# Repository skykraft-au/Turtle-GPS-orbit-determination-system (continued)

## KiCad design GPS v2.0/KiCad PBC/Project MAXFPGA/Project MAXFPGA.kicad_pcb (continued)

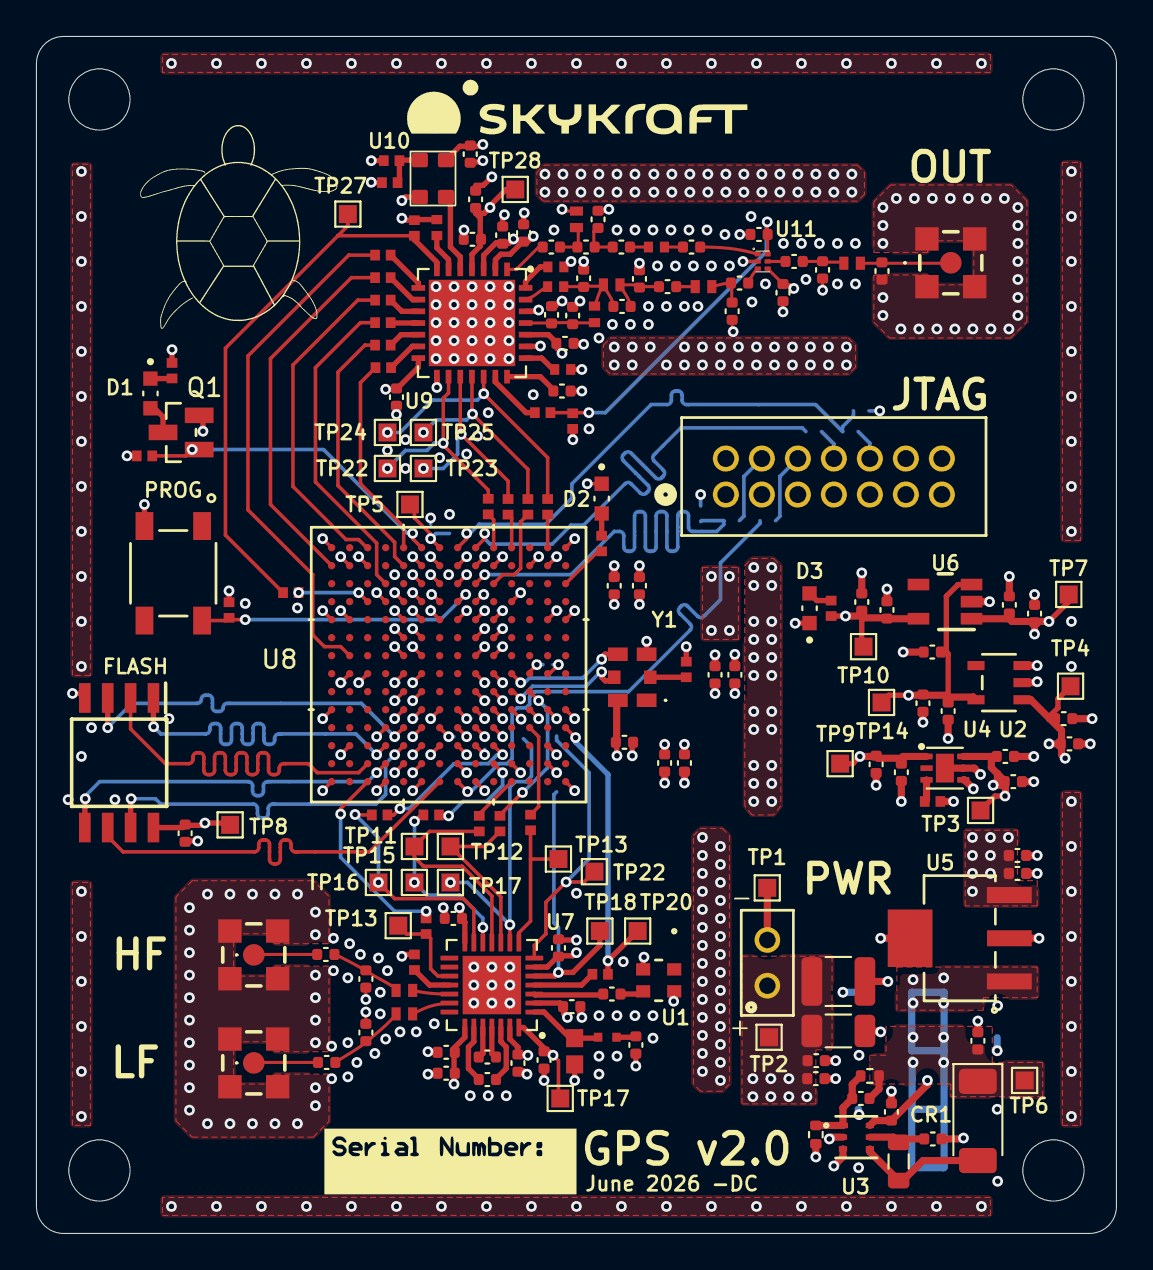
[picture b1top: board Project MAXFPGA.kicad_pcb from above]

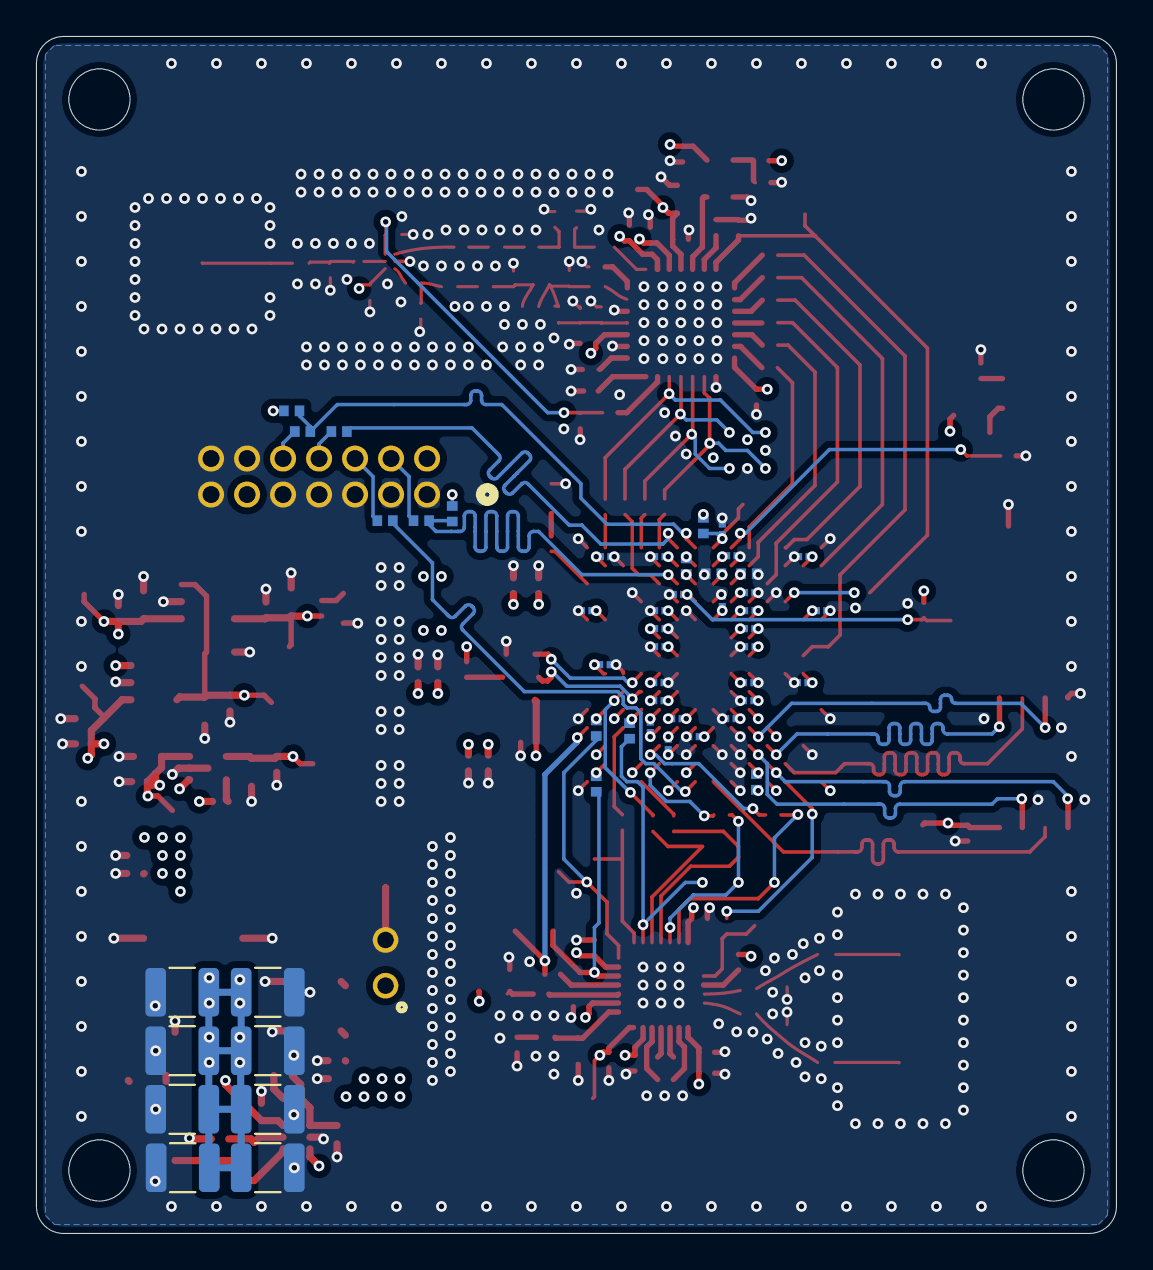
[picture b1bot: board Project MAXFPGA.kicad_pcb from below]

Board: 4 copper layers, 60.0 x 66.5 mm, 221 parts (49 on the bottom side), 117 nets.

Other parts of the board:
FLASH: MT25QL128ABA1ESE-0SIT_TR; SOIC127P790X216-8N
HF: MMCX-J-P-H-ST-SM1; MMCXJPHSTSM1
JTAG: 878311420; JTAG_Conn
LF: MMCX-J-P-H-ST-SM1; MMCXJPHSTSM1
OUT: MMCX-J-P-H-ST-SM1; MMCXJPHSTSM1
PROG: PTS647SK38SMTR2LFS; PTS647SK38SMTR2LFS_CNK
PWR: Conn_01x02_Pin; CONN2_M20-999_1x2_HRW

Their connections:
3.3v Post: FLASH.8 (VCC), JTAG.2; also elsewhere on the board
+3.3V: PWR.1; also elsewhere on the board
FLASH CHIP SELECT: FLASH.1 (S#); also elsewhere on the board
FLASH Clock: FLASH.6 (C); also elsewhere on the board
FLASH D0: FLASH.5 (DQ0); also elsewhere on the board
FLASH D1: FLASH.2 (DQ1); also elsewhere on the board
FLASH D2: FLASH.3 (W#/DQ2); also elsewhere on the board
FLASH D3: FLASH.7 (HOLD#/DQ3); also elsewhere on the board
FPGA PROGRAM: PROG.2; also elsewhere on the board
GND: FLASH.4 (VSS), HF.2, HF.3, HF.4, HF.5, JTAG.1, JTAG.3, JTAG.5, JTAG.7, JTAG.9, JTAG.12, JTAG.13, JTAG.14, LF.2, LF.3, LF.4, LF.5, OUT.2, OUT.3, OUT.4, OUT.5, PROG.3, PWR.2; also elsewhere on the board
unnamed 46: HF.1; also elsewhere on the board
unnamed 47: LF.1; also elsewhere on the board
unnamed 60: OUT.1; also elsewhere on the board
unnamed 65: JTAG.4; also elsewhere on the board
unnamed 66: JTAG.6; also elsewhere on the board
unnamed 67: JTAG.8; also elsewhere on the board
unnamed 68: JTAG.10; also elsewhere on the board
